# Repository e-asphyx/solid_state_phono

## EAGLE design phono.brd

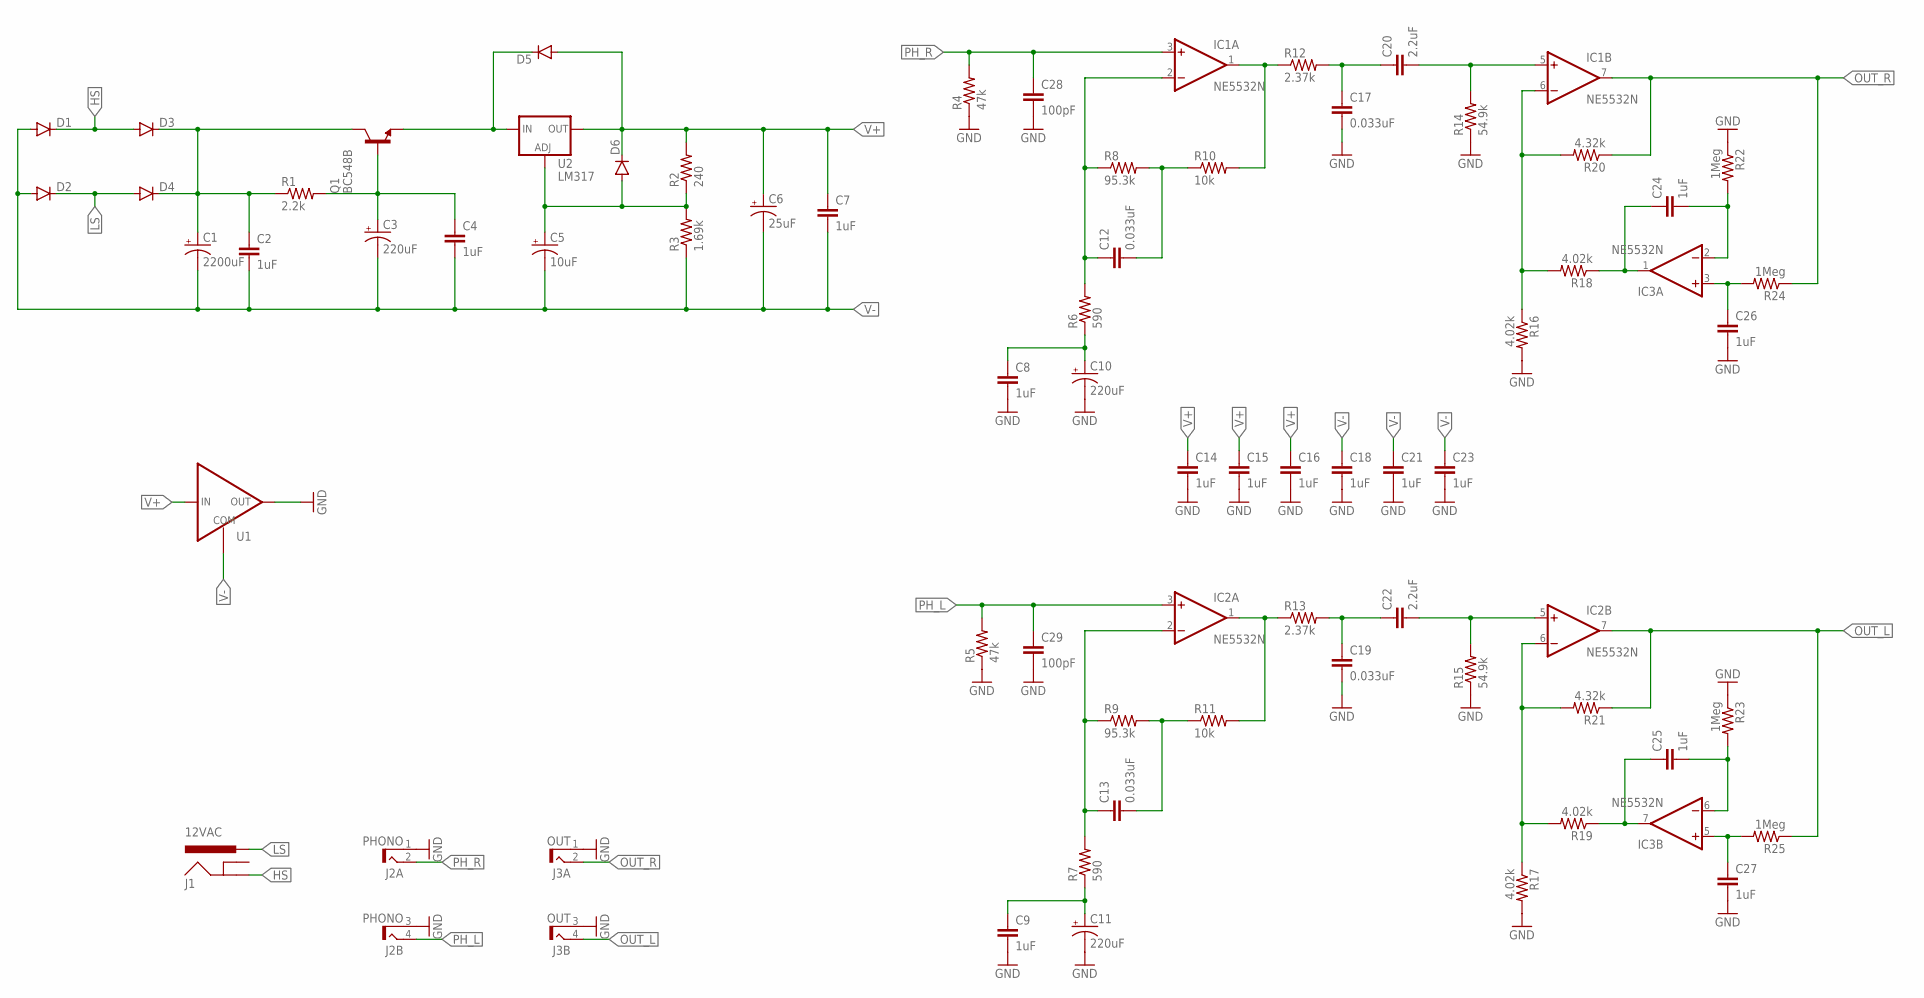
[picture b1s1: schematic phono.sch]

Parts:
C1: 2200uF; CPOL-RADIAL-1000UF-25V
C2, C4, C7, C8, C9, C14, C15, C16, C18, C21, C23: 1uF; CAP-PTH-SMALL
C3, C10, C11: 220uF; E3,5-8
C5: 10uF; CPOL-RADIAL-10UF-25V
C6: 25uF; CPOL-RADIAL-10UF-25V
C12, C13, C17, C19: 0.033uF; C5B7.2; MOUSER_ID 505-FKP20.033/63/2.5
C20, C22: 2.2uF; C5B7.2; MOUSER_ID 505-MKS22.2/63/5
C24, C25, C26, C27: 1uF; C5B5.5
C28, C29: 100pF; C5B4.5
D1, D2, D3, D4, D5, D6: DIODEPTH; DIODE-1N4001
IC1, IC2, IC3: NE5532N; DIL08
J1: 12VAC; POWER_JACK_PTH
J2: PHONO; RCJ-21
J3: OUT; RCJ-21
Q1: BC548B; TO92-EBC
R1: 2.2k; AXIAL-0.4
R2: 240; AXIAL-0.4
R3: 1.69k; AXIAL-0.4
R4, R5: 47k; AXIAL-0.4
R6, R7: 590; AXIAL-0.4
R8, R9: 95.3k; AXIAL-0.4
R10, R11: 10k; AXIAL-0.4
R12, R13: 2.37k; AXIAL-0.4
R14, R15: 54.9k; AXIAL-0.4
R16, R17, R18, R19: 4.02k; AXIAL-0.4
R20, R21: 4.32k; AXIAL-0.4
R22, R23, R24, R25: 1Meg; AXIAL-0.4
U1: TLE2426-3; TO92-BENT
U2: LM317; V-REG_DPACK

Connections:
FB2_L: IC2.6 (-IN), R17.P$1 (1), R19.P$2 (2), R21.P$2 (2)
FB2_R: IC1.6 (-IN), R16.P$1 (1), R18.P$2 (2), R20.P$2 (2)
FB_L: C13.1, IC2.2 (-IN), R7.P$2 (2), R9.P$1 (1)
FB_R: C12.1, IC1.2 (-IN), R6.P$2 (2), R8.P$1 (1)
GND: C8.2, C9.2, C10.-, C11.-, C14.2, C15.2, C16.2, C17.2, C18.2, C19.2, C21.2, C23.2, C26.2, C27.2, C28.2, C29.2, J2.1 (S), J2.3 (S), J3.1 (S), J3.3 (S), R4.P$1 (1), R5.P$1 (1), R14.P$1 (1), R15.P$1 (1), R16.P$2 (2), R17.P$2 (2), R22.P$1 (1), R23.P$1 (1), U1.1 (OUT)
HS: D1.C, D3.A, J1.GND
LS: D2.C, D4.A, J1.PWR
unnamed: IC1.1 (OUT), R10.P$2 (2), R12.P$1 (1)
unnamed: C12.2, R8.P$2 (2), R10.P$1 (1)
unnamed: D5.C, Q1.E, U2.3 (IN)
unnamed: C17.1, C20.1, R12.P$2 (2)
unnamed: C20.2, IC1.5 (+IN), R14.P$2 (2)
unnamed: C8.1, C10.+, R6.P$1 (1)
unnamed: IC2.1 (OUT), R11.P$2 (2), R13.P$1 (1)
unnamed: C24.1, IC3.1 (OUT), R18.P$1 (1)
unnamed: C3.+, C4.1, Q1.B, R1.P$2 (2)
unnamed: C24.2, IC3.2 (-IN), R22.P$2 (2)
unnamed: C26.1, IC3.3 (+IN), R24.P$2 (2)
unnamed: C13.2, R9.P$2 (2), R11.P$1 (1)
unnamed: C9.1, C11.+, R7.P$1 (1)
unnamed: C19.1, C22.1, R13.P$2 (2)
unnamed: C22.2, IC2.5 (+IN), R15.P$2 (2)
unnamed: C25.1, IC3.7 (OUT), R19.P$1 (1)
unnamed: C25.2, IC3.6 (-IN), R23.P$2 (2)
unnamed: C27.1, IC3.5 (+IN), R25.P$2 (2)
unnamed: C5.1 (+), D6.A, R2.P$1 (1), R3.P$2 (2), U2.1 (ADJ)
unnamed: C1.+, C2.1, D3.C, D4.C, Q1.C, R1.P$1 (1)
OUT_L: IC2.7 (OUT), J3.4 (T), R21.P$1 (1), R25.P$1 (1)
OUT_R: IC1.7 (OUT), J3.2 (T), R20.P$1 (1), R24.P$1 (1)
PH_L: C29.1, IC2.3 (+IN), J2.4 (T), R5.P$2 (2)
PH_R: C28.1, IC1.3 (+IN), J2.2 (T), R4.P$2 (2)
V+: C6.1 (+), C7.1, C14.1, C15.1, C16.1, D5.A, D6.C, IC1.8 (V+), IC2.8 (V+), IC3.8 (V+), R2.P$2 (2), U1.3 (IN), U2.4 (OUT)
V-: C1.-, C2.2, C3.-, C4.2, C5.2 (-), C6.2 (-), C7.2, C18.1, C21.1, C23.1, D1.A, D2.A, IC1.4 (V-), IC2.4 (V-), IC3.4 (V-), R3.P$1 (1), U1.2 (COM)

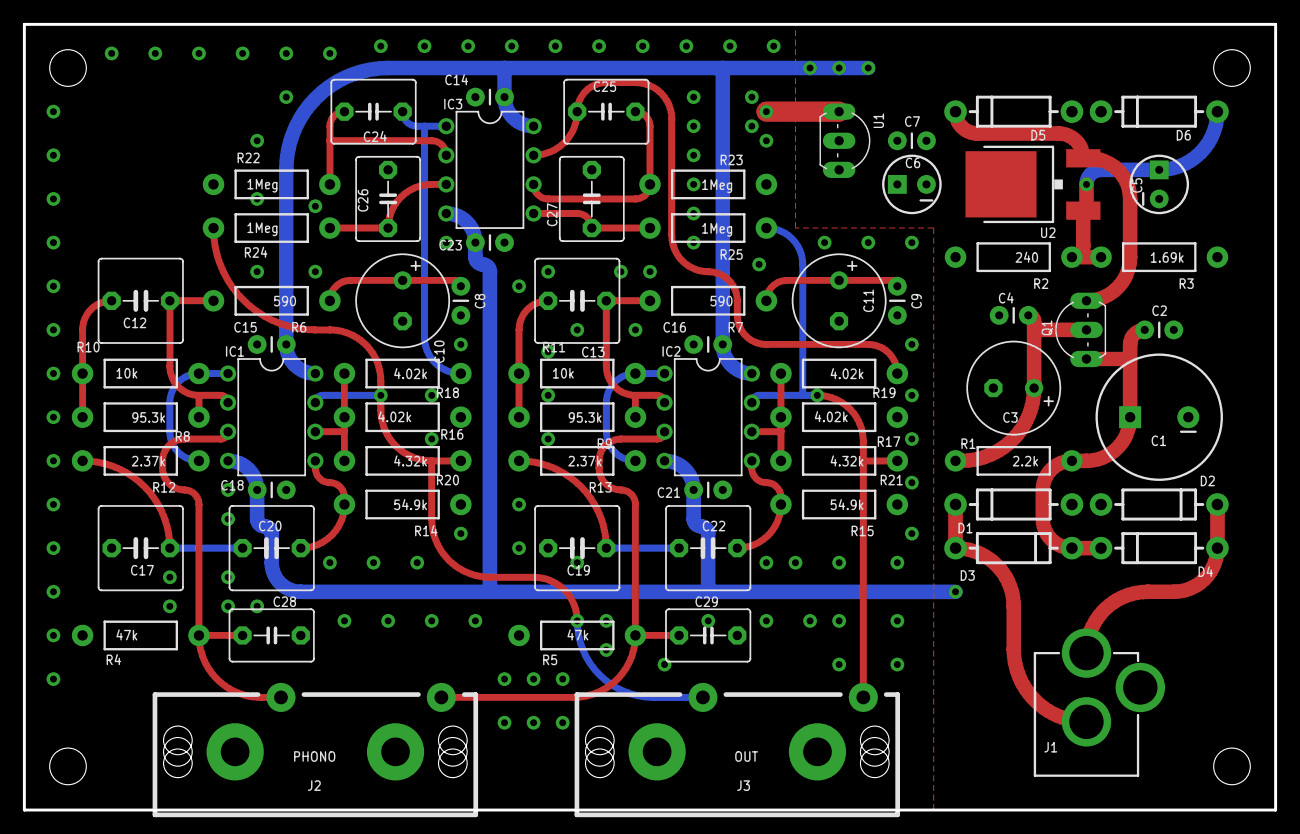
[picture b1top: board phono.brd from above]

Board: 2 copper layers, 109.2 x 68.6 mm, 69 parts (0 on the bottom side), 33 nets.

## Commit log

2016-10-05 Initial
2016-10-05 Some tweaks
2016-10-05 PDFs
2016-10-05 100p input shunt
2016-10-05 Measures

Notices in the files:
parts and their libraries:
SparkFun-Connectors: Licensing: Creative Commons ShareAlike 4.0 International - https://creativecommons.org/licenses/by-sa/4.0
